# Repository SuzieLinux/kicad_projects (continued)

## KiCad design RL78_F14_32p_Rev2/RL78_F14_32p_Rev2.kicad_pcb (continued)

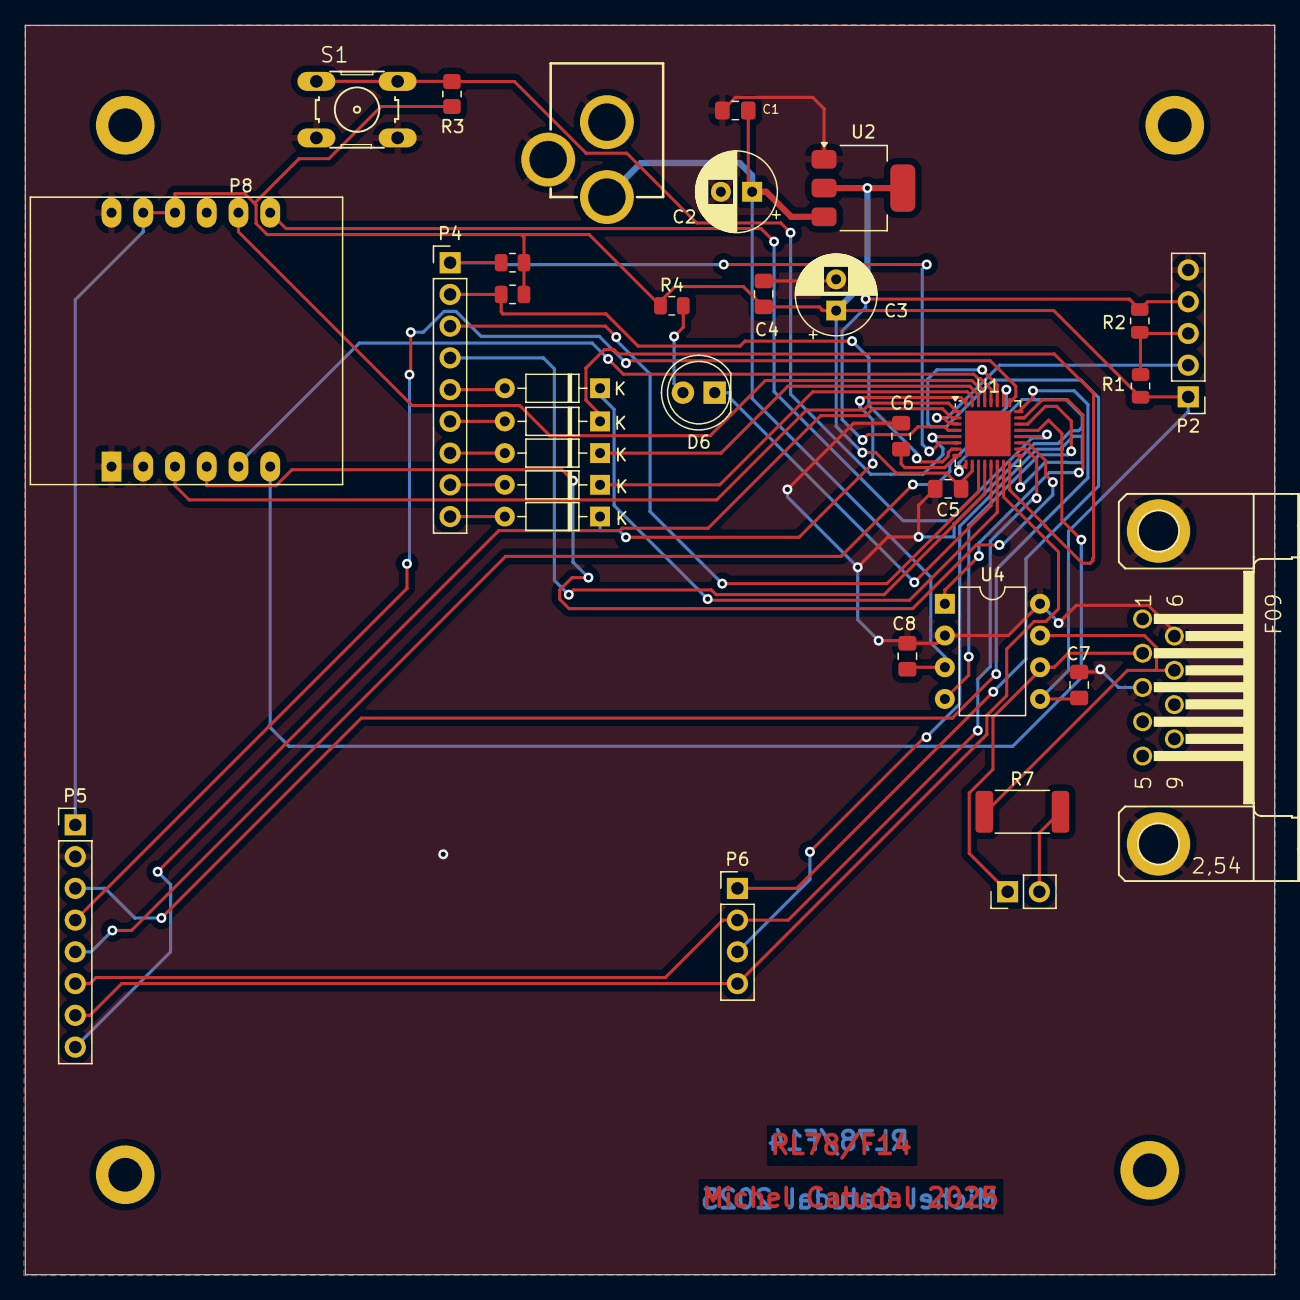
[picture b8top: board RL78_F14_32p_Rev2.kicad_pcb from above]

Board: 2 copper layers, 100.0 x 100.0 mm, 37 parts (0 on the bottom side), 43 nets.

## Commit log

2025-01-12 Create README.md
    This repository contains kicad projects created with version 8.0 on Arch Linux and Gentoo Linux
2025-01-12 Added LICENCE and README.md files
2025-01-12 Added projects for Beagleplay and Beagle-AI-64
2025-01-12 Added Beagley-ai CAN projects
2025-01-12 Added missing word in README.md file
2025-01-13 Added lcd adapter board
2025-01-14 Added USB to J1587 board as well as a CAN adapter if your board has no CAN
2025-01-14 Added usb to lin board
2025-01-15 Added a RL78 G14/G24 project
2025-01-16 Added RL78/F14 project and added jumper for the 120 ohms resistors in the G24 project
2025-01-16 Fixed errors for Keypad for RL78 F14 board with on board CAN Ports 12.1 and 12.2 do no provide pullups but Port 6.0 and 6.1 do Resistors removed for port 6 since internal pullups can be used Basicall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
2025-01-16 Added a board that uses a 48 pins F14
2025-01-17 Removed backups accidentally saved
2025-01-17 OOPS! P130 is write only and I had it set as input for the LCD board
2025-01-18 Added a few projects
2025-01-19 Added a few other projects
2025-01-19 Added two more projects
2025-04-09 Added pocketbeagle2 cape
2025-04-09 Added the mounting holes
2025-04-10 Last commit seemed to have trashed the files, lucky I had a backupd
2025-04-10 Added a board to connect an Arduino LCD to something else and another PocketBeagle2 Cape
